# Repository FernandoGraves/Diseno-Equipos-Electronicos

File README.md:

# Diseno-Equipos-Electronicos
Entregas 2023-2

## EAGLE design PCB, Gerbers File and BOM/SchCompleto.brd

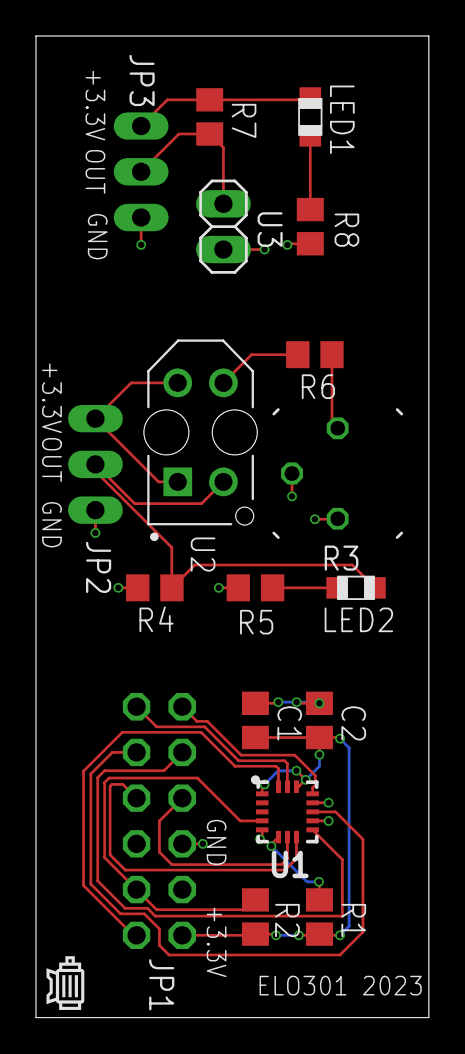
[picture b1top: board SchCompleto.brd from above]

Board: 2 copper layers, 21.8 x 54.5 mm, 18 parts (0 on the bottom side), 19 nets.

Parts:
C1: 100nF; C0805
C2: 10uF; C0805
JP1: 2X06/90
JP2, JP3: 1X03
LED1, LED2: CHIP-LED0805
R1, R2: 10k; R0805
R3: 5kΩ; CT6
R4, R7: 3.3kΩ; R0805
R5, R8: 100Ω; R0805
R6: 50Ω; R0805
U1: LIS3DHTR; LGA-16-3X3
U2: TCRT5000L; PCBMOUNT
U3: SENSOR_TEMPERATURA; 1X02

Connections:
+3V3: C1.1, C2.1, JP1.1, R1.2, R2.2, U1.1, U1.14
ADC1: JP1.2, U1.16
ADC2: JP1.12, U1.15
ADC3: JP1.11, U1.13
CS: JP1.8, U1.8
GND: C1.2, C2.2, JP1.5, JP2.1, JP3.1, R3.A, R3.S, R4.1, R5.1, R8.2, U1.5, U1.10, U1.12, U3.2
INT1: JP1.10, U1.11
INT2: JP1.9, U1.9
LED1_R8: LED1.C, R8.1
OUT2: JP2.2, LED2.A, R4.2, U2.2
OUT3: JP3.2, R7.2, U3.1
R3_R6: R3.E, R6.1
R5_LED2: LED2.C, R5.2
R6_TCRT: R6.2, U2.3
SCL/SPC: JP1.4, R2.1, U1.4
SDA/SDI/SDO: R1.1, U1.6
SDO/SA0: JP1.7, U1.7
VCC: JP2.3, U2.1, U2.4
VDD: JP3.3, LED1.A, R7.1

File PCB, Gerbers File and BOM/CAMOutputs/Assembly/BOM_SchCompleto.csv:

Qty;Value;Device;Package;Parts;Description;PARTNO;POPULARITY;SPICEPREFIX
2;;LEDCHIP-LED0805;CHIP-LED0805;LED1, LED2;LED;EAST2012GA0;68;
2;;PINHD-1X3;1X03;JP2, JP3;PIN HEADER;PPPC031LFBN-RC;92;
1;;PINHD-2X6/90;2X06/90;JP1;PIN HEADER;PPPC062LJBN-RC;1;
1;100nF;C-USC0805;C0805;C1;CAPACITOR, American symbol;GCM21BR72A104KA37L;63;C
2;100Ω;R-EU_R0805;R0805;R5, R8;RESISTOR, European symbol;RC0805FR-07100RL;86;R
2;10k;R-US_R0805;R0805;R1, R2;RESISTOR, American symbol;RC0805FR-0710KL;85;R
1;10uF;C-USC0805;C0805;C2;CAPACITOR, American symbol;EDK106M035A9BAA;63;C
2;3.3kΩ;R-EU_R0805;R0805;R4, R7;RESISTOR, European symbol;RC0402FR-073K3L;86;R
1;50Ω;R-EU_R0805;R0805;R6;RESISTOR, European symbol;RT0805FRE0751RL;86;R
1;5kΩ;TRIM_EU-CT6;CT6;R3;POTENTIOMETER;CT-6EP502;1;
1;LIS3DHTR;LIS3DHTR;LGA-16-3X3;U1;;LIS3DHTR;;
1;SENSOR_TEMPERATURA;SENSOR_TEMPERATURA;1X02;U3;;NTCLE305E4103SB;;
1;TCRT5000L;TCRT5000L;PCBMOUNT;U2;TCRT5000 Series 940 nm 100 mA 60 mA Transistor Output Reflective Optical Sensor;TCRT5000L;;
;;;;;;;;
;;;;;;;;
;;;;;;;;
;;;;;;;;
;;;;;;;;
;;;;;;;;
;;;;;;;;
